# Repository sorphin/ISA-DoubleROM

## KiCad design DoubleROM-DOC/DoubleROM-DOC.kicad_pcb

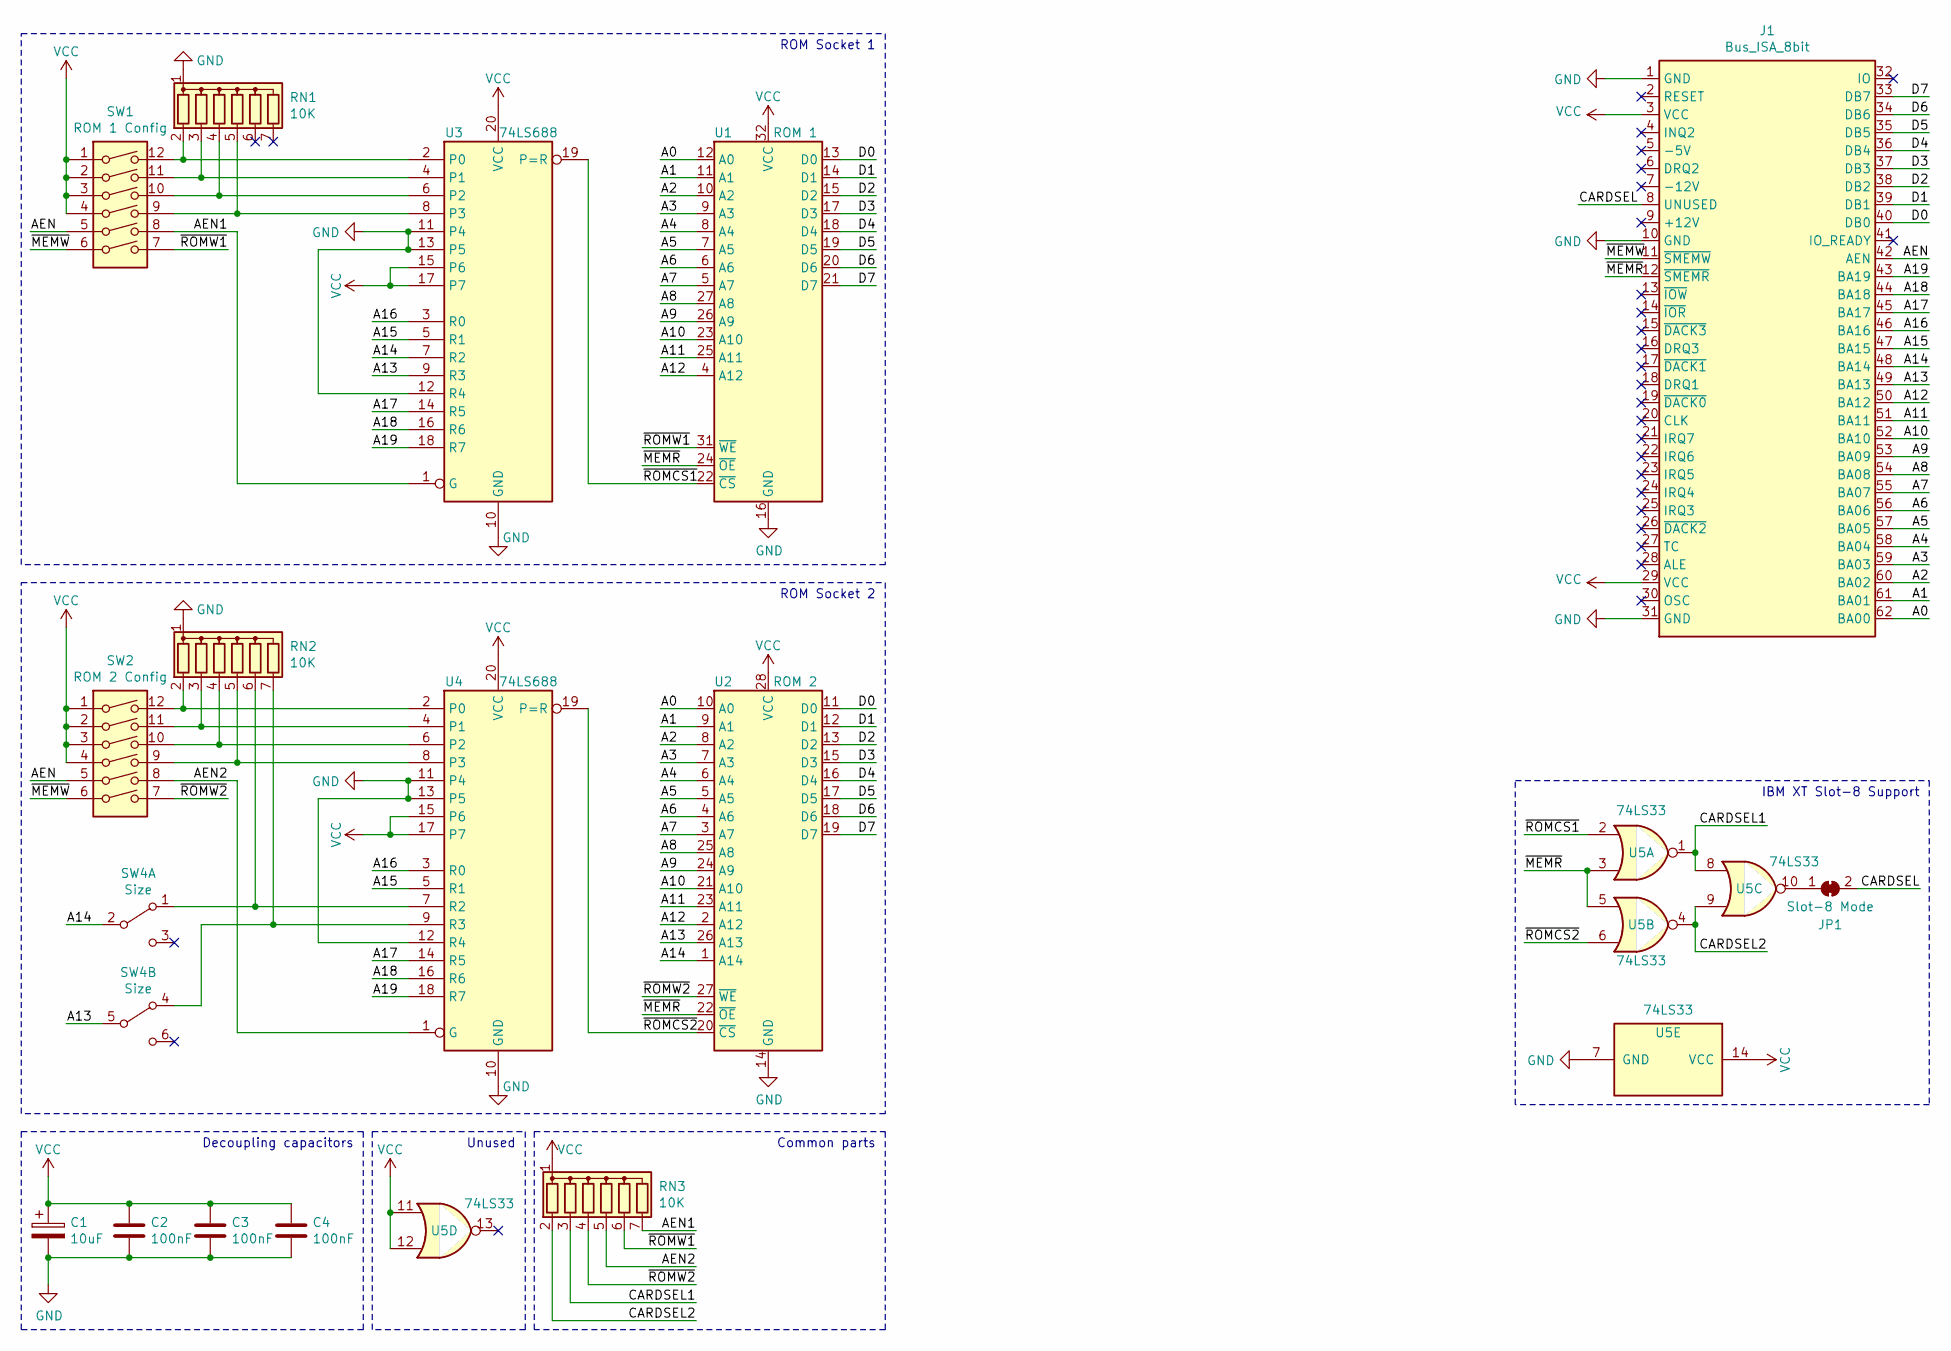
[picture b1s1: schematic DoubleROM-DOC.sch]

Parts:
C1: 10uF; CP_Radial_Tantal_D4.5mm_P5.00mm
C2, C3, C4: 100nF; C_Disc_D4.3mm_W1.9mm_P5.00mm
J1: Bus_ISA_8bit; Conn_Bus_ISA8
JP1: Slot-8 Mode; SolderJumper-2_P1.3mm_Bridged_RoundedPad1.0x1.5mm
RN1, RN2, RN3: 10K; R_Array_SIP7
SW1: ROM 1 Config; SW_DIP_SPSTx06_Slide_9.78x17.42mm_W7.62mm_P2.54mm
SW2: ROM 2 Config; SW_DIP_SPSTx06_Slide_9.78x17.42mm_W7.62mm_P2.54mm
SW4: Size; SW_MS-22D18G2
U1: ROM 1; DIP-32_W15.24mm_Socket
U2: ROM 2; DIP-28_W15.24mm_Socket
U3, U4: 74LS688; DIP-20_W7.62mm
U5: 74LS33; SOIC-14_3.9x8.7mm_P1.27mm

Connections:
/A0: J1.62 (BA00), U1.12 (A0), U2.10 (A0)
/A1: J1.61 (BA01), U1.11 (A1), U2.9 (A1)
/A2: J1.60 (BA02), U1.10 (A2), U2.8 (A2)
/A3: J1.59 (BA03), U1.9 (A3), U2.7 (A3)
/A4: J1.58 (BA04), U1.8 (A4), U2.6 (A4)
/A5: J1.57 (BA05), U1.7 (A5), U2.5 (A5)
/A6: J1.56 (BA06), U1.6 (A6), U2.4 (A6)
/A7: J1.55 (BA07), U1.5 (A7), U2.3 (A7)
/A8: J1.54 (BA08), U1.27 (A8), U2.25 (A8)
/A9: J1.53 (BA09), U1.26 (A9), U2.24 (A9)
/A10: J1.52 (BA10), U1.23 (A10), U2.21 (A10)
/A11: J1.51 (BA11), U1.25 (A11), U2.23 (A11)
/A12: J1.50 (BA12), U1.4 (A12), U2.2 (A12)
/A13: J1.49 (BA13), SW4.5 (B), U2.26 (A13), U3.9 (R3)
/A14: J1.48 (BA14), SW4.2 (B), U2.1 (A14), U3.7 (R2)
/A15: J1.47 (BA15), U3.5 (R1), U4.5 (R1)
/A16: J1.46 (BA16), U3.3 (R0), U4.3 (R0)
/A17: J1.45 (BA17), U3.14 (R5), U4.14 (R5)
/A18: J1.44 (BA18), U3.16 (R6), U4.16 (R6)
/A19: J1.43 (BA19), U3.18 (R7), U4.18 (R7)
/AEN: J1.42 (AEN), SW1.5, SW2.5
/AEN1: RN3.7 (R6), SW1.8, U3.1 (G)
/AEN2: RN3.5 (R4), SW2.8, U4.1 (G)
/CARDSEL: J1.8 (UNUSED), JP1.2 (B)
/CARDSEL1: RN3.3 (R2), U5.1, U5.8
/CARDSEL2: RN3.2 (R1), U5.4, U5.9
/D0: J1.40 (DB0), U1.13 (D0), U2.11 (D0)
/D1: J1.39 (DB1), U1.14 (D1), U2.12 (D1)
/D2: J1.38 (DB2), U1.15 (D2), U2.13 (D2)
/D3: J1.37 (DB3), U1.17 (D3), U2.15 (D3)
/D4: J1.36 (DB4), U1.18 (D4), U2.16 (D4)
/D5: J1.35 (DB5), U1.19 (D5), U2.17 (D5)
/D6: J1.34 (DB6), U1.20 (D6), U2.18 (D6)
/D7: J1.33 (DB7), U1.21 (D7), U2.19 (D7)
/~MEMR: J1.12 (~SMEMR), U1.24 (~OE), U2.22 (~OE), U5.3, U5.5
/~MEMW: J1.11 (~SMEMW), SW1.6, SW2.6
/~ROMCS1: U1.22 (~CS), U3.19 (P=R), U5.2
/~ROMCS2: U2.20 (~CS), U4.19 (P=R), U5.6
/~ROMW1: RN3.6 (R5), SW1.7, U1.31 (~WE)
/~ROMW2: RN3.4 (R3), SW2.7, U2.27 (~WE)
GND: C1.2, C2.2, C3.2, C4.2, J1.1 (GND), J1.10 (GND), J1.31 (GND), RN1.1 (common), RN2.1 (common), U1.16 (GND), U2.14 (GND), U3.10 (GND), U3.11 (P4), U3.12 (R4), U3.13 (P5), U4.10 (GND), U4.11 (P4), U4.12 (R4), U4.13 (P5), U5.7 (GND)
unnamed: JP1.1 (A), U5.10
unnamed: RN1.2 (R1), SW1.12, U3.2 (P0)
unnamed: RN1.3 (R2), SW1.11, U3.4 (P1)
unnamed: RN1.4 (R3), SW1.10, U3.6 (P2)
unnamed: RN1.5 (R4), SW1.9, U3.8 (P3)
unnamed: RN2.2 (R1), SW2.12, U4.2 (P0)
unnamed: RN2.3 (R2), SW2.11, U4.4 (P1)
unnamed: RN2.4 (R3), SW2.10, U4.6 (P2)
unnamed: RN2.5 (R4), SW2.9, U4.8 (P3)
unnamed: RN2.6 (R5), SW4.1 (A), U4.7 (R2)
unnamed: RN2.7 (R6), SW4.4 (A), U4.9 (R3)
VCC: C1.1, C2.1, C3.1, C4.1, J1.3 (VCC), J1.29 (VCC), RN3.1 (common), SW1.1, SW1.2, SW1.3, SW1.4, SW2.1, SW2.2, SW2.3, SW2.4, U1.32 (VCC), U2.28 (VCC), U3.15 (P6), U3.17 (P7), U3.20 (VCC), U4.15 (P6), U4.17 (P7), U4.20 (VCC), U5.11, U5.12, U5.14 (VCC)

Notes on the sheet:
Unused
Decoupling capacitors
IBM XT Slot-8 Support
ROM Socket 1
ROM Socket 2
Common parts

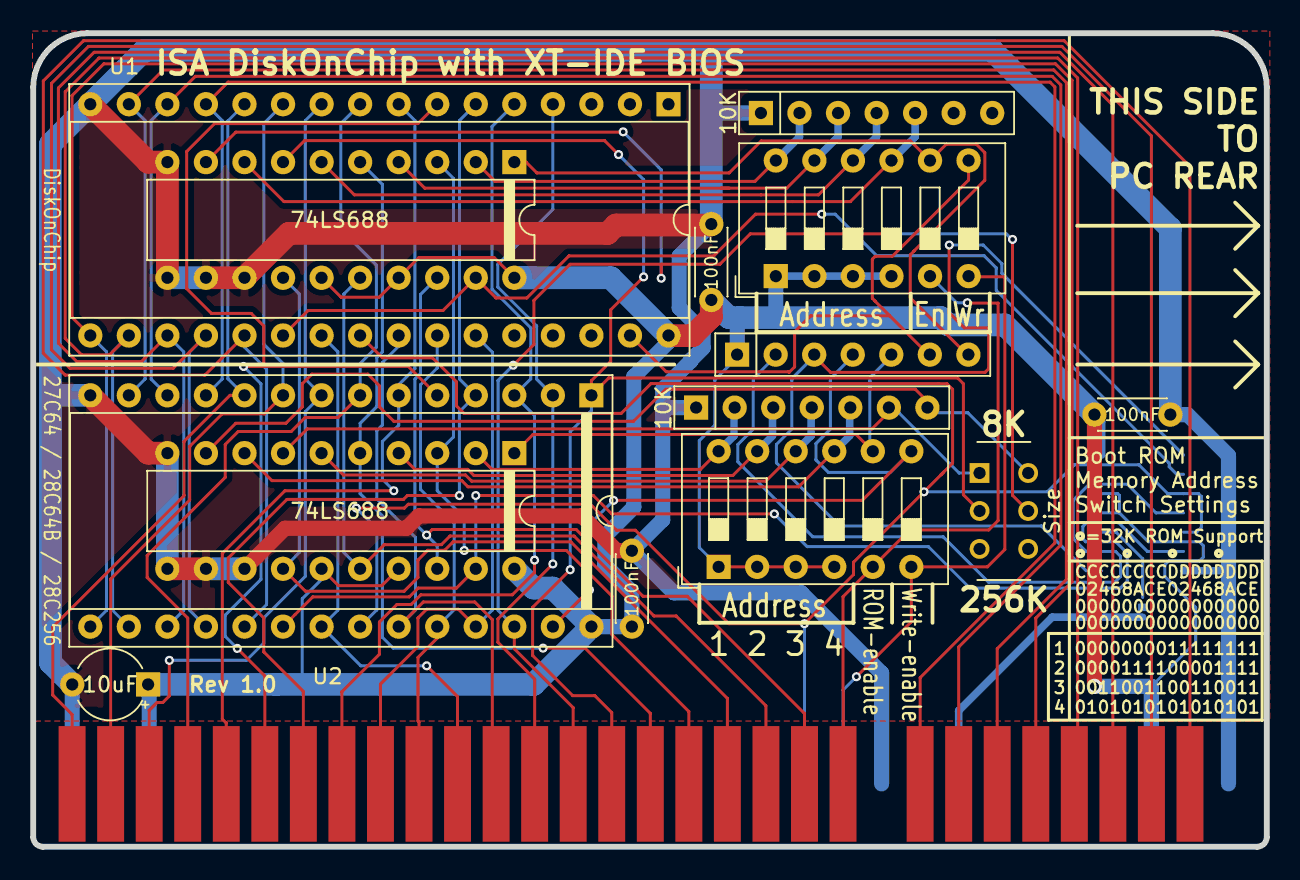
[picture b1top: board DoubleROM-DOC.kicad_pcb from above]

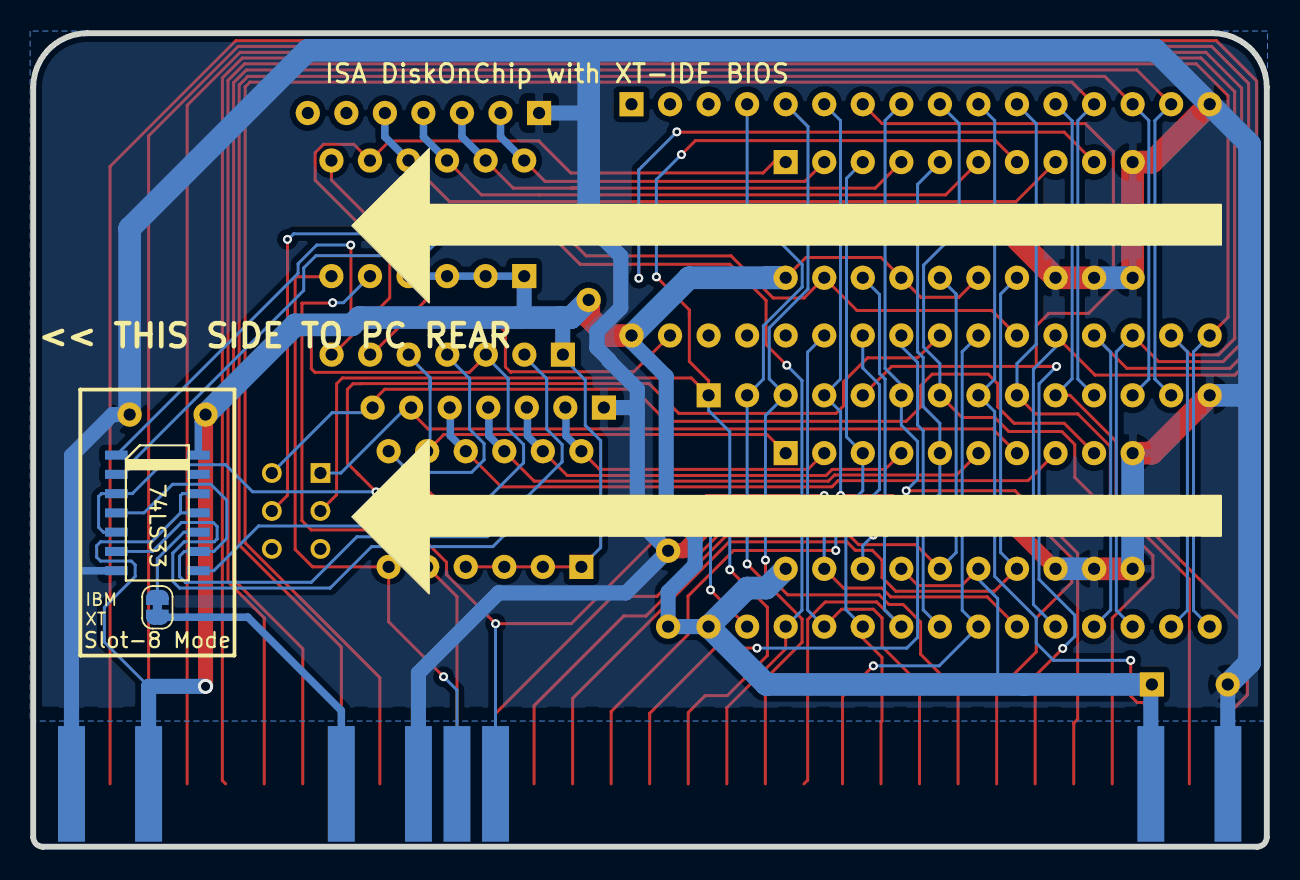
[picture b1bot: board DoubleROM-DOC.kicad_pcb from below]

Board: 2 copper layers, 81.3 x 53.6 mm, 17 parts (2 on the bottom side), 53 nets.

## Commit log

2023-06-12 Add files via upload
    Revised DoubleRom board to have 1 ROM socket and a DiskOnChip Socket. Tested working. May add activity LED in future.
2023-06-12 Corrected schematic info to reflect DOC addition
2023-06-21 Sunc up PDF and .sch schematic file.
